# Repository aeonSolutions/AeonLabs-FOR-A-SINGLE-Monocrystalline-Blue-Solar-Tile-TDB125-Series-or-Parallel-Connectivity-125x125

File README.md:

[PCB-Prototyping-Catalogue](https://github.com/aeonSolutions/PCB-Prototyping-Catalogue)  >>  [Home-Automation](https://github.com/aeonSolutions/PCB-Prototyping-Catalogue/tree/main/Home-Automation)  >>  [Smart Home Solar Power Management](https://github.com/aeonSolutions/PCB-Prototyping-Catalogue/tree/main/Home-Automation/Smart%20Home%20Solar%20Power%20Management)  >>  Single Monocrystalline Blue Solar Tile TDB125 Series or Parallel Connectivity 125x125mm

<br>

<p align="right">
 <a href="https://github-com.translate.goog/aeonSolutions/PCB-Prototyping-Catalogue/tree/main?_x_tr_sl=en&_x_tr_tl=pt&_x_tr_hl=en&_x_tr_pto=wapp">Change Language</a> <br>
Last update: 01-12-2023
</p>

# Single Monocrystalline Blue Solar Tile TDB125 Series or Parallel Connectivity 125x125mm

This is a simple PCB for a direct fit on commercially available [blue solar cell tiles](https://s.click.aliexpress.com/e/_DCnJW0V)  with dimensions 124x124mm. This PCB is intended to give support and stregth to the fragile solar tile while allowing in series or parallel connectivty with orther solar tiles. Is designed within mind installation on the top or downside of transparent glass windows at a home or office. This PCB, when assembled with a blue solar cell tile, can be used to power a low voltage 4.2V indoor illumination network using ultra-low power micro LED strips.  For insatnce [this one](https://s.click.aliexpress.com/e/_DCKg9xJ) sold on AliExpress.   

When connected in series and installed on several windows and networked, can power off the grid a 4.2V LED illumination on all rooms and compartments at a home or office. During evenings and at night until bedtime. If one intends to use it to power indoors LED illumination during the day is required a High Capacity Power Bank connected to all first tiles of all the series. For instance this [power bank](https://s.click.aliexpress.com/e/_Ddl7nsh) here. 

One important take way about this prototype project is in the ability to be installed on any traditional apartment or home in a big city, requiring  124mm of window glass estate, at the top or at the bottom. And it can connect to existing home automation network or systems. 

<p align="center">

</p>

A breif view of specifications:

- the PCB can be connected in series to form a lenght of solar cell tiles packed together (each with its own single BMS. 
- PCB asssembly in series made with a 10 pin pin header/ socket. For "plug and play" type of instalations
- Screw terminal to connect main low power 5V DC line at home/office. 

<br>

**Status**

waiting to be tested. Stay tuned for updates.

<br>

## PCB

<br>

## Compatibility

<p align="center">

</p>

<br>

## What one additionally needs
-  home tools
-  [transparent double sided tape](https://s.click.aliexpress.com/e/_DDJxMmD)
-  [blue solar cell tiles](https://s.click.aliexpress.com/e/_DCnJW0V)
-  [ultra-low power micro LED strips](https://s.click.aliexpress.com/e/_DCKg9xJ) 
-  [ultra-low power  LED Cob strips](https://s.click.aliexpress.com/e/_DnqkC4N)
-  [Nylon Guide for Electric Cable](https://s.click.aliexpress.com/e/_DBc1oVX)
-  [NCR18650B 3.7V 3400 mah 18650 Lithium](https://s.click.aliexpress.com/e/_DCh1sw1)
-  [Low power electrical wire](https://s.click.aliexpress.com/e/_DB1T3eN)
-  [16A Electrical Plug Wall Socket 110~250V Dual USB 2000mA Port](https://s.click.aliexpress.com/e/_DlVz3sh)
-  [Soldering iron](https://s.click.aliexpress.com/e/_DnDN8x3)
-  [Solder](https://s.click.aliexpress.com/e/_DlXtKMN)
- [power bank](https://s.click.aliexpress.com/e/_Ddl7nsh) 

<br />
<br />

## Author

You can get in touch with me on my LinkedIn Profile:

#### Miguel Tomas

You can also follow my GitHub Profile to stay updated about my latest projects: 

<br>

### Be supportive of my dedication and work towards technology education and buy me a cup of coffee
The PCB Desgin Files i provide here for anyone to use are free. If you like this Smart Device or use it, please consider buying me a cup of coffee, a slice of pizza or a book to help me study, eat and think new PCB design files.

<br />

### Make a donation on Paypal
Make a donation on paypal and get a TAX refund*.

<br>

### Support all these open hardware projects and become a patreon  
Liked any of my PCB KiCad Designs? Help and Support my open work to all by becomming a LDAD Patreon.
In return I will give a free PCB design in KiCad to all patreon supporters. To learn more go to patreon.com. Link below.

<br />
<br />

______________________________________________________________________________________________________________________________
### License
Before proceeding to download any of AeonLabs software solutions for open-source development and/or PCB hardware electronics development make sure you are choosing the right license for your project. See [AeonLabs Solutions for Open Hardware & Source Development](https://github.com/aeonSolutions/PCB-Prototyping-Catalogue/wiki/AeonLabs-Solutions-for-Open-Hardware-&-Source-Development) for more information.

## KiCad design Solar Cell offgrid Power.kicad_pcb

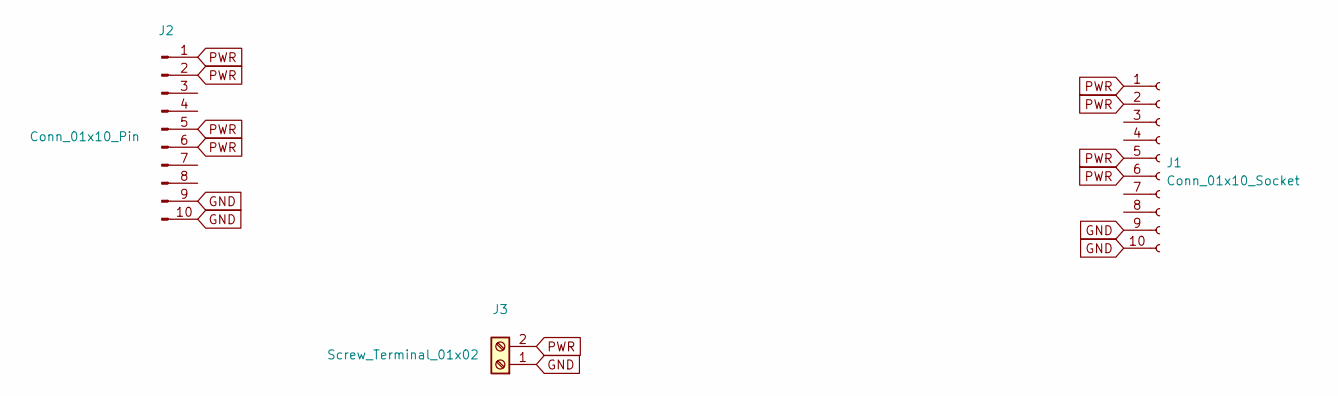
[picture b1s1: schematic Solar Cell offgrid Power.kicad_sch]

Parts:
J1: Conn_01x10_Socket; PinSocket_1x10_P2.54mm_Horizontal
J2: Conn_01x10_Pin; PinHeader_1x10_P2.54mm_Horizontal
J3: Screw_Terminal_01x02; TerminalBlock_Phoenix_MPT-0,5-2-2.54_1x02_P2.54mm_Horizontal

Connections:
GND: J1.9, J1.10, J2.9, J2.10, J3.1
PWR: J1.1, J1.2, J1.5, J1.6, J2.1, J2.2, J2.5, J2.6, J3.2

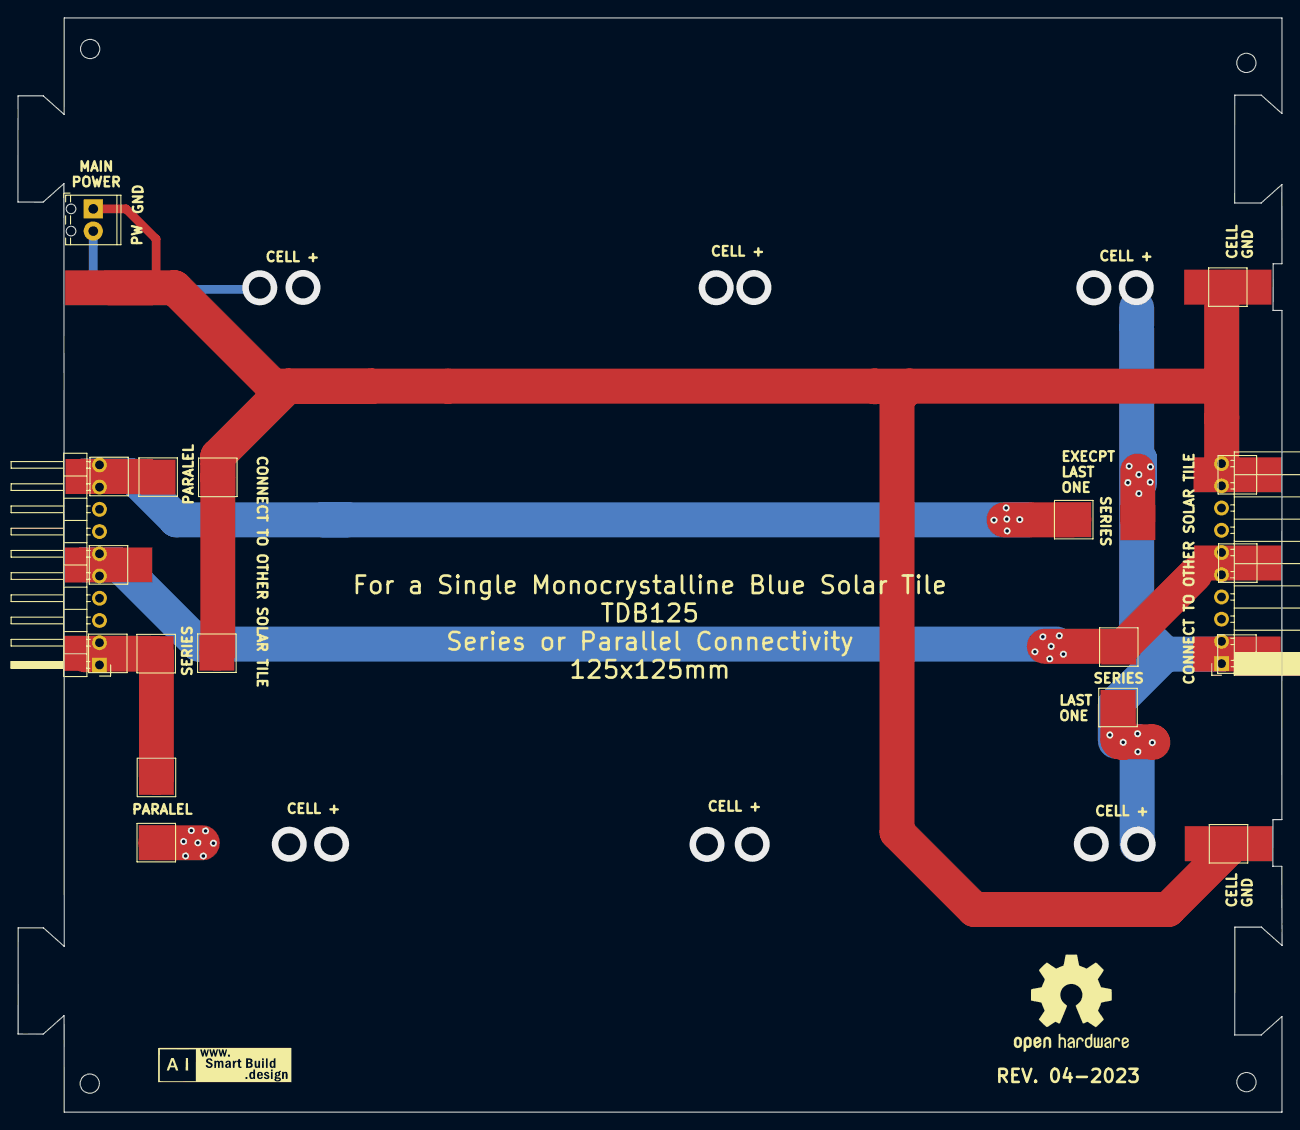
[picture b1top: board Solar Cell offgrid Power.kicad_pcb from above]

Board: 2 copper layers, 144.5 x 125.1 mm, 3 parts (0 on the bottom side), 2 nets.
